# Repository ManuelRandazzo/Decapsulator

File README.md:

# Decapsulator

<p align="center">
  <em>Repo condiviso con il Gruppo 1 ITS 24-26 con programma del macchinario</em>
</p>

---

## Overview
**Decapsulator** è il prototipo di un macchinario nato con lo scopo principale di ridurre rifiuti secchi automatizzando un processo ripetitivo, che tende ad essere evitato e talvolta può diventare pericoloso se non si prestano le dovute attenzioni che è quello di aprire le capsule esauste per poter separare il caffè dall'involucro esterno.

**Sedi**: 
- **IIS Einaudi-Scarpa** : Via Sansovino, 6, 31044 Montebelluna (TV)
- **IPSIA Barsanti-Galilei** : Via Avenale, 6, 31033 Castelfranco Veneto (TV) 

---

## Intended Use 
Prototipo a scopo didattico, non destinato alla vendita o all'uso continuativo. In caso di vendita a scopo commerciale saranno da integrare tutti i dispositivi di sicurezza descritti nelle norme vigenti nella data di revisione e modifica del prototipo successiva a quella descritta dal documento di uso e manutenzione. 

---

## Features
- Automatizzazione della separazione delle capsule dal caffè
- Orientato alla facilità di utilizzo e di manutenzione
- FreeRTOS per avere un controllo real time del processo
- Sicurezza del macchinario
- Prototipo modulabile per diversi tipi di capsule cambiando pochissimi componenti
- Il suo sviluppo ha contribuito in piccola parte al mondo dell'Open Hardware di disegni CAD 3D.
- Design compatto rivolto ad un ambiente domestico

---

## Authors
- ***Manuel Randazzo*** - Firmware Designer, Backend Firmware Developer, Integration Developer, Firmware Tester, Electrical Designer, Electrical tester, Mechanical Designer, Documentation Contributor.
- ***Alessio Pisan*** - Electrical Designer, Electrical Tester, Frontend Firmware Developer, Backend Firmware Developer, Firmware Tester, Documentation Contributor.
- ***Riccardo Pavanetto*** - Mechanical Designer, Mechanical Designer
- ***Federico Dorigo*** - Scrum Master, Procurement Coordinator, Documentation Coordinator, Payroll Administrator
- ***Christian Poletti*** - Documentation Contributor
- ***Arun James Thanamcheril*** - Documentation Contributor

<p align="center">
    <em>Foto del gruppo 1 ITS 24-25 - foto scattata nel 2025.</em>
    <em>Partendo da sinistra : Manuel, Christian, Alessio, Riccardo e Federico</em>
</p>

<p align="center">
    <em>Foto del gruppo 1 ITS 25-26 - foto scattata nel 2026.</em>
    <em>Partendo da sinistra : Federico, Christian, Riccardo, Arun James, Manuel e Alessio</em>
</p>

---

## Dichiarazione Di Conformità CE Del Prototipo
Il presente prototipo è stato progettato seguendo i criteri di sicurezza delle varie direttive:  
- ***Direttiva Macchine 2006/42/CE***: Poiché l'apparecchio presenta organi in movimento, tra cui tamburo rotante, paratia di selezionatura servo-attivata e punzone, i quali comportano rischi meccanici.

- ***Direttiva Bassa Tensione (LVD) 2014/35/UE***: Consultata per la sicurezza dei componenti elettrici e dei circuiti di alimentazione.

- ***Direttiva Compatibilità Elettromagnetica (EMC) 2014/30/UE***: Applicabile per garantire che l’elettronica non interferisca con altre apparecchiature circostanti al macchinario.

- ***Direttiva RoHS 2011/65/UE***: Consultata per garantire l'assenza di sostanze pericolose nei componenti elettronici e nei materiali di apporto. 

Norme armonizzate applicate :
- ***UNI EN ISO 12100:2010***: Sicurezza del macchinario - Principi generali di progettazione - Valutazione e attenuazione del rischio. 

- ***UNI EN ISO 13857:2020***: Distanze di sicurezza per impedire il raggiungimento di zone pericolose con gli arti superiori (utilizzata per dimensionare l'imbocco delle capsule e i carter del tamburo).

- ***UNI EN ISO 14119:2013***: Dispositivi di interblocco associati ai ripari (utilizzata per la scelta e l'installazione del micro-switch di sicurezza sul coperchio).

- ***CEI EN 60204-1***: Sicurezza dell'equipaggiamento elettrico delle macchine (utilizzata per lo schema elettrico e funzionale). 

---

## Disegno Prototipo E Componenti Principali
- ### **Parte Meccanica**

<p align="center">
  <em>Figura 1 — Architettura generale del Decapsulator</em>
</p>
 
**Tabella Componenti :**

| N° |  Descrizione  |
|----|---------------|
| 1  | Profili in alluminio 30x30 cm |
| 2  | Magazzino verticale capsule |
| 3  | Paratia di selezionatura servoattivata del magazzino verticale |
| 4  | Tamburo di posizionamento |
| 5  | Zona di Punzonatura e Raschiatura |
| 6  | Motore passo-passo del Punzone e Raschiatore |
| 7  | Display dell’interfaccia uomo-macchina (HMI) |
| 8  | Scheda elettronica |
| 9  | Griglia di protezione parte elettronica |
| 10 | Ventola di raffreddamento (lato sinistro del macchinario) |

<p align="center">
  <em>Figura 2 — Magazzino Cialde : Serve per stoccare le capsule prima che vengano </em>
</p>

<p align="center">
  <em>Figura 3 — Tamburo : Serve per trasportare la capsula nelle varie fasi di lavorazione (Acquisizione, Punzonatura, Raschiatura, Espulsione)</em>
</p>

- ### **Parte Elettronica**

<p align="center">
  <em>Figura 4 — Scheda di controllo del Decapsulator</em>
</p>

<p align="center">
  <em>Figura 5 — Scheda HMI del Decapsulator</em>
</p>

<p align="center">
  <em>Figura 5 — Scheda HMI del Decapsulator - Vista retro</em>
</p>

<p align="center">
  <em>Figura 6 — Schede del "Magazzino Cialde" del Decapsulator, rappresentano due foto transistor e due LED IR, inoltre su una scheda è presente il connettore 3 poli del servomotore della "Paratia"</em>
</p>

---

## Sequenza Di Funzionamento Automatico Del Decapsulator
Il "Decapsulator" quando viene pilotato in modalità automatica per aprire le capsule di caffè segue questo diagramma :

Il quale temporalmente si traduce in questa sequenza osservando i componenti :

---

## Dati Sui Motori Utilizzati
Le librerie del driver DRV8825 sono state sviluppate interamente da Manuel Randazzo il quale si è preoccupato di studiare e testare l'hardware, consultare la documentazione ufficiale per poter integrare al meglio la libreria che può essere inclusa così :
```C++
#include "DRV8825_Decapsulator.hpp"
```
oppure includendo la libreria del Motion Controller che già utilizza internamente la precedente libreria e che permette una gestione più semplice del Motore :
```C++
#include "MotionControl.hpp"
```

**Flow chart MotionController**

<p align="center">
  <em>Figura 7 — Flow chart MotionController</em>
</p>

**Simulazione Grafico Coppia-Velocità Motori Stepper**

<p align="center">
  <em>Figura 8 — Simulazione curva di coppia dei motori stepper con MATLAB</em>
</p>

---

## Diagnostica E Troubleshooting
Vi è una sezione dedicata per accedere alle impostazioni del manutentore direttamente dall'HMI del macchinario.

Per aiutare il manutentore ad individuare i problemi è possibile ottenere dei privilegi elevati attraverso un login e di conseguenza accedere alla pagina di diagnostica composta dal registro eventi (***Log***) del macchinario e dal movimento manuale (***Jog***) dei motori passo-passo del tamburo rotante e del punzone.

Per maggiori informazioni riguardo a come utilizzare la pagina di manutenzione consultare il manuale di uso e manutenzione alla sezione ***"9.4 Manutenzione tramite pagina di diagnostica sull’interfaccia utente"***.

- Come accedere alla pagina di diagnostica dalla GUI:  

1. Individuare nella pagina principale l’icona dell’ingranaggio indicata in figura

2. Inserire la password unica fornita ai manutentori specializzati

- Come navigare nella pagina di diagnostica dalla GUI, riferimento alla sezione 9.4 del manuale di uso e manutenzione:  

1. Se si vogliono visualizzare i ***LOG*** del macchinario premere il pulsante "Logger" in alto a sinistra della pagina di diagnostica come in figura:

1.1. Una volta selezionato il Logger si vedrà questa pagina da cui si potrà refreshare i logs oppure cancellarli per avere una pagina più pulita con i tasti in figura:

2. Se si vogliono comandare in modalità manuale i motori del macchinario con il ***JOG*** premere il pulsante "Jogger" in alto a destra della pagina di diagnostica come in figura:

2.1. Nota: non sarà possibile aggedere alla pagina "Jogger" se il ciclo automatico è stato avviato e non è stato messo in STOP oppure non è finito e si potrà vedere il seguente messaggio:

2.2. Una volta selezionato il Jogger si vedrà questa pagina da cui si potrà comandare indipendemente i motori e visualizzare gli stati dei sensori di finecorsa:

3. Se si vuole calibrare il display touch premere il pulsante in basso a sinistra della pagina di diagnostica e seguire le istruzioni fornite a display come in figura:

4. Se si vogliono inserire nuove credenziali per il WiFi premere il pulsante in basso a destra della pagina di diagnostica come in figura:

4.1. Una volta selezionata la pagina di configurazione del WiFi verrà visualizzata questa pagina:

<p align="center">
  <em>Nota : il WiFi consente al macchinario di fare l'upload del firmware tramite Over The Air (OTA), di far loggare in MQTT i messaggi del macchinario e soprattutto di sincronizzare il Real Time Clock (RTC) tramite server NTP così da visualizzare l'ora esatta</em>
</p>

---

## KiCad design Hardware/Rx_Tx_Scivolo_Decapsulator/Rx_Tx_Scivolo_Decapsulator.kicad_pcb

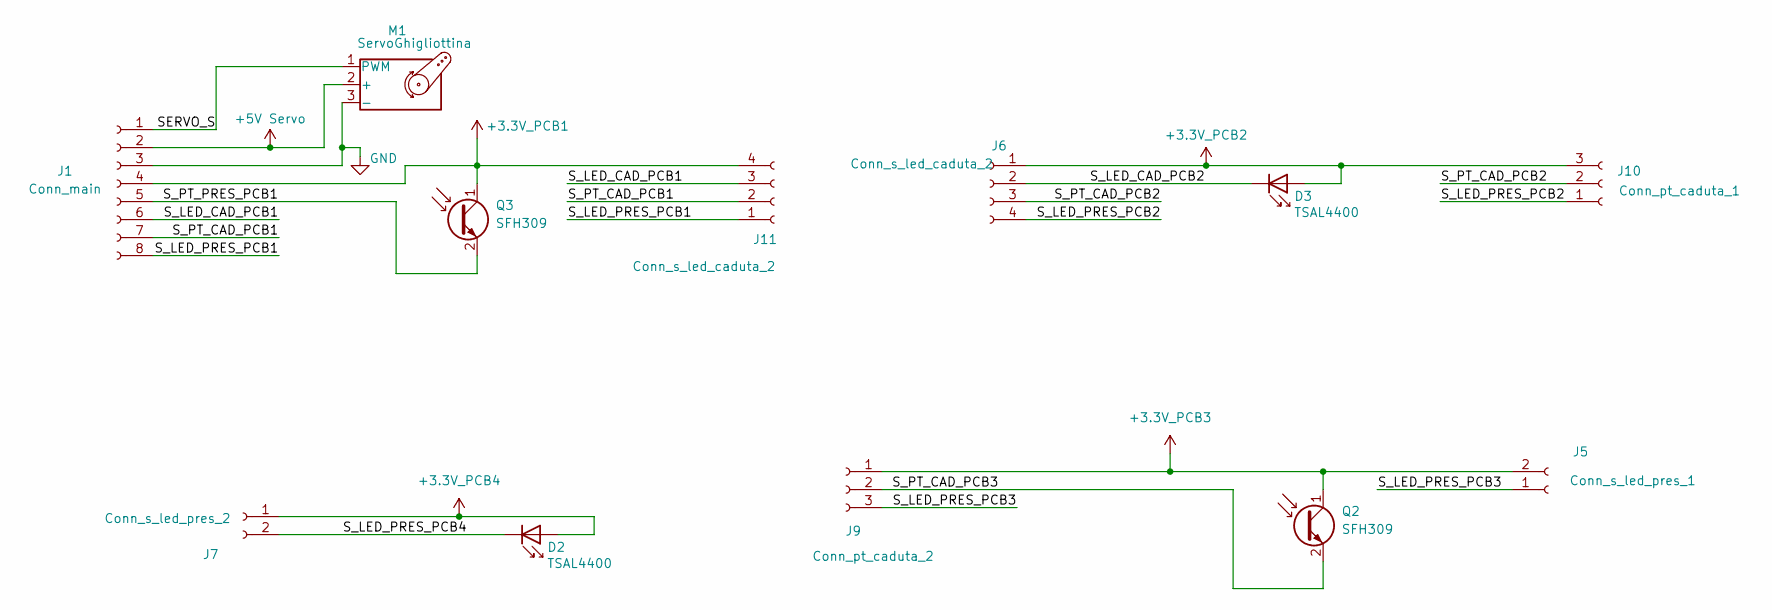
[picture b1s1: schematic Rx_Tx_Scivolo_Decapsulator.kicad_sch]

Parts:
D2, D3: TSAL4400; LED_D3.0mm_Clear
J1: Conn_main; JST_PH_S8B-PH-SM4-TB_1x08-1MP_P2.00mm_Horizontal
J5: Conn_s_led_pres_1; JST_PH_S2B-PH-SM4-TB_1x02-1MP_P2.00mm_Horizontal
J6, J11: Conn_s_led_caduta_2; JST_PH_S4B-PH-SM4-TB_1x04-1MP_P2.00mm_Horizontal
J7: Conn_s_led_pres_2; JST_PH_S2B-PH-SM4-TB_1x02-1MP_P2.00mm_Horizontal
J9: Conn_pt_caduta_2; JST_PH_S3B-PH-SM4-TB_1x03-1MP_P2.00mm_Horizontal
J10: Conn_pt_caduta_1; JST_PH_S3B-PH-SM4-TB_1x03-1MP_P2.00mm_Horizontal
M1: ServoGhigliottina; PinHeader_1x03_P2.54mm_Vertical_SMD_Pin1Right
Q2, Q3: SFH309; LED_D3.0mm_IRBlack

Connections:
+3.3V_PCB1: J1.4, J11.4, Q3.1 (C)
+3.3V_PCB2: D3.2 (A), J6.1, J10.3
+3.3V_PCB3: J5.2, J9.1, Q2.1 (C)
+3.3V_PCB4: D2.2 (A), J7.1
+5V Servo: J1.2, M1.2 (+)
/SERVO_S: J1.1, M1.1 (PWM)
/S_LED_CAD_PCB1: J1.6, J11.3
/S_LED_CAD_PCB2: D3.1 (K), J6.2
/S_LED_PRES_PCB1: J1.8, J11.1
/S_LED_PRES_PCB2: J6.4, J10.1
/S_LED_PRES_PCB3: J5.1, J9.3
/S_LED_PRES_PCB4: D2.1 (K), J7.2
/S_PT_CAD_PCB1: J1.7, J11.2
/S_PT_CAD_PCB2: J6.3, J10.2
/S_PT_CAD_PCB3: J9.2, Q2.2 (E)
/S_PT_PRES_PCB1: J1.5, Q3.2 (E)
GND: J1.3, J1.MP, M1.3 (-)

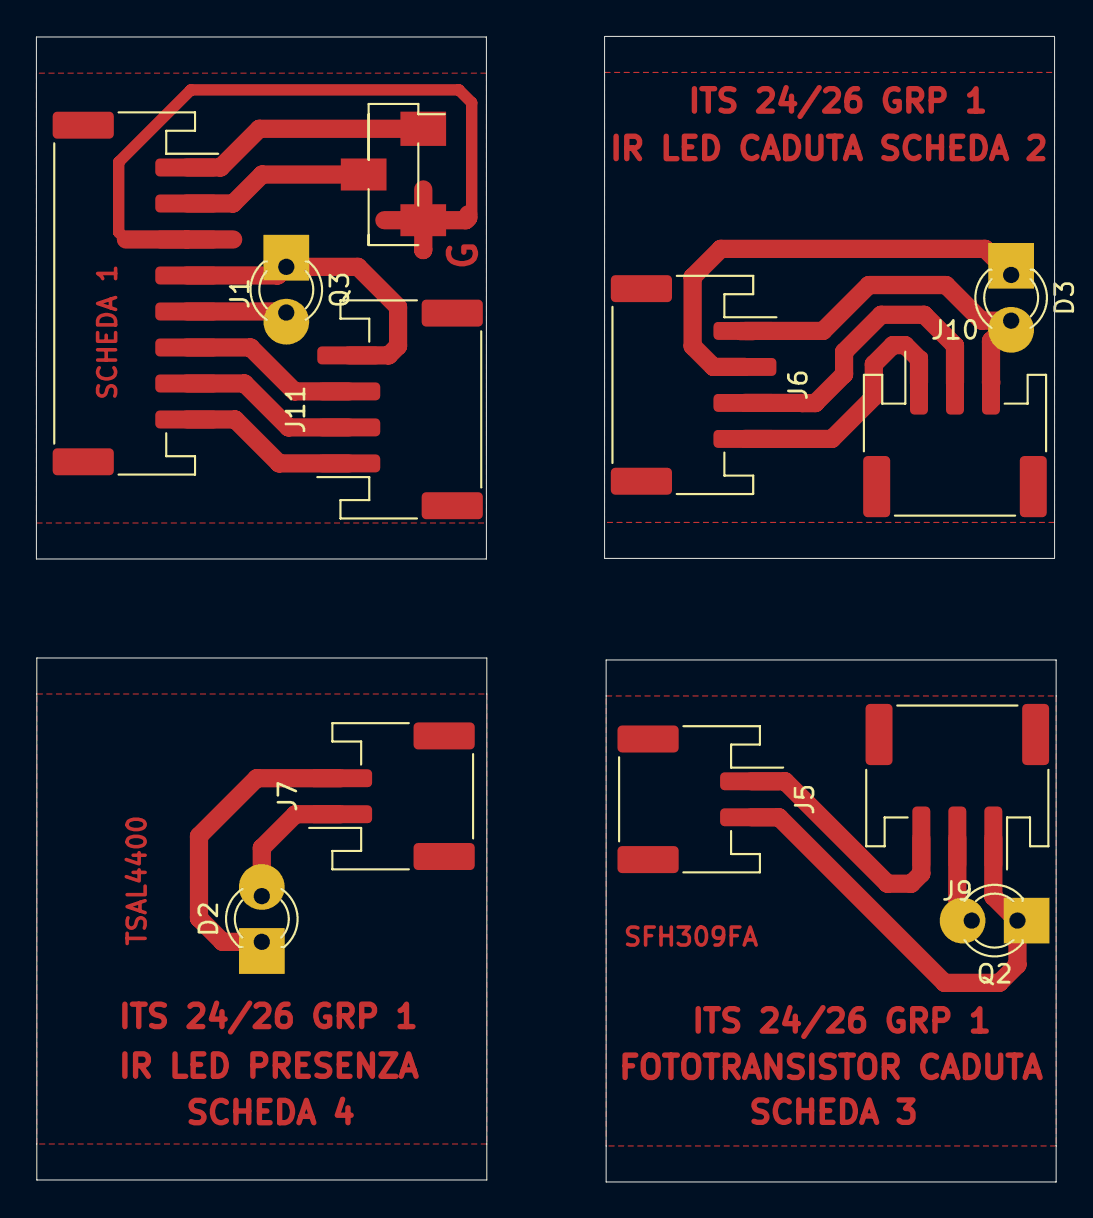
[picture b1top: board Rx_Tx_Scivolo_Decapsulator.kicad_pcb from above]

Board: 2 copper layers, 56.7 x 63.6 mm, 12 parts (0 on the bottom side), 17 nets.

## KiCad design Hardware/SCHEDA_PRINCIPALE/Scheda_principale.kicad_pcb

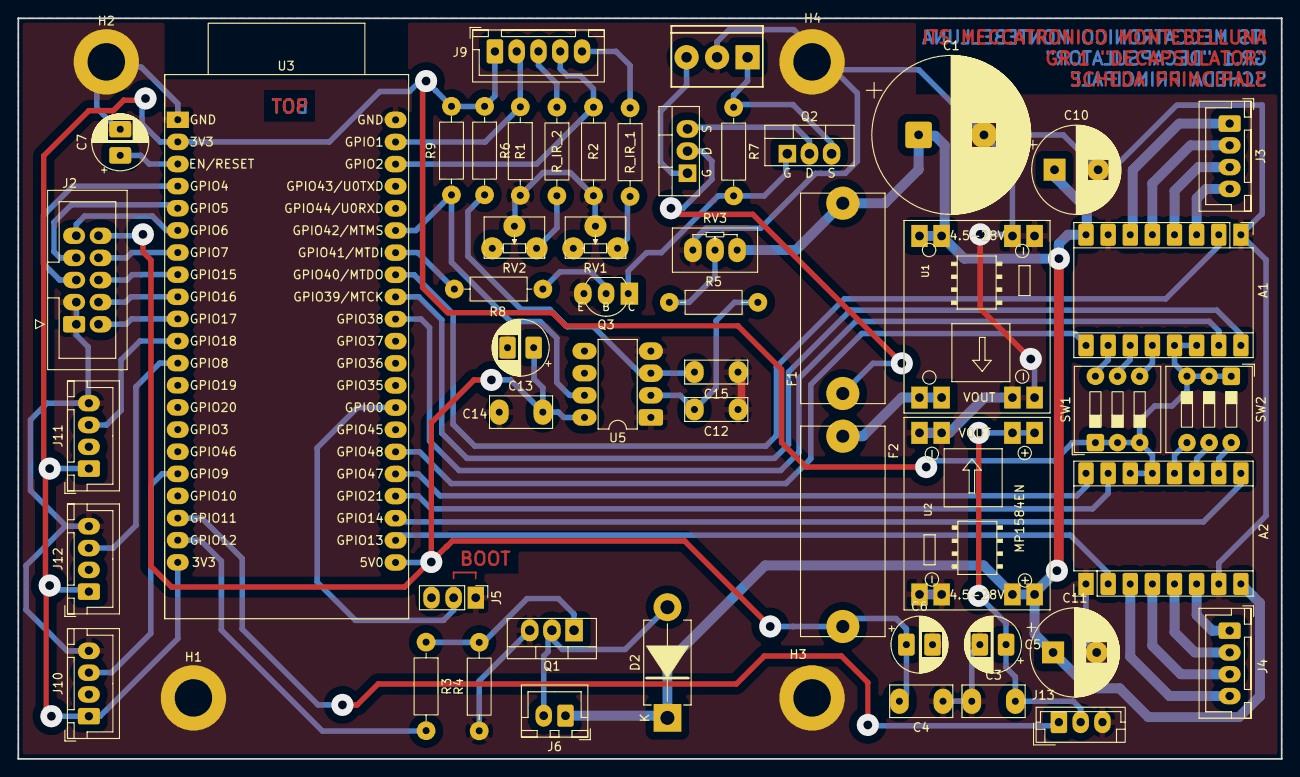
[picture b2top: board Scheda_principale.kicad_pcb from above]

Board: 2 copper layers, 145.0 x 85.0 mm, 56 parts (0 on the bottom side), 61 nets.

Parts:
A1: Driver_motore_ralla; DRV8825
A2: Driver_motore_Punz; DRV8825
C1: 4700uF; CP_Radial_D18.0mm_P7.50mm
C3, C4: 330nF; C_Rect_L7.0mm_W3.5mm_P5.00mm
C5, C6, C13: 47uF; CP_Radial_D6.3mm_P2.50mm
C7: 10uF; CP_Radial_D6.3mm_P2.50mm
C10, C11: 470uF 35V; CP_Radial_D10.0mm_P5.00mm
C12, C15: 22nF; C_Rect_L7.0mm_W2.5mm_P5.00mm
C14: 100nF; C_Rect_L7.0mm_W3.5mm_P5.00mm
D1: SDT10A100CT; TO-220-3_Vertical_GDS
D2: 1N5822; D_DO-201AD_P12.70mm_Horizontal
F1, F2: Fuse; FUSE_4527
H1, H2, H3, H4: MountingHole_Pad; MountingHole_4.3mm_M4_DIN965_Pad
J1: Screw_Terminal_01x03; ScrewTerminal_1x03_P3.5mm_Blue
J2: Conn HMI; IDC-Header_2x05_P2.54mm_Vertical
J3: Conn_Mot_Ralla; JST_XH_B4B-XH-A_1x04_P2.50mm_Vertical
J4: Conn_Mot_Punz; JST_XH_B4B-XH-A_1x04_P2.50mm_Vertical
J5: Conn_BT_MCU; PinHeader_1x03_P2.54mm_Vertical
J6: Conn_Vent1; JST_XH_B2B-XH-A_1x02_P2.50mm_Vertical
J9: Conn_Phototrans; JST_XH_B5B-XH-A_1x05_P2.50mm_Vertical
J10: Conn_hall1; JST_XH_B4B-XH-A_1x04_P2.50mm_Vertical
J11: Conn_hall2; JST_XH_B4B-XH-A_1x04_P2.50mm_Vertical
J12: Conn_hall3; JST_XH_B4B-XH-A_1x04_P2.50mm_Vertical
J13: Conn_Servo; JST_EH_B3B-EH-A_1x03_P2.50mm_Vertical
Q1: IRLZ44N; TO-220-3_Vertical
Q2: IRF9540N; TO-220-3_Vertical_GDS
Q3: BC547B
R1, R2: 47k; R_Axial_DIN0207_L6.3mm_D2.5mm_P10.16mm_Horizontal
R3: 220; R_Axial_DIN0207_L6.3mm_D2.5mm_P10.16mm_Horizontal
R4: 10k; R_Axial_DIN0207_L6.3mm_D2.5mm_P10.16mm_Horizontal
R5, R6: 47K; R_Axial_DIN0207_L6.3mm_D2.5mm_P10.16mm_Horizontal
R7: 15k; R_Axial_DIN0207_L6.3mm_D2.5mm_P10.16mm_Horizontal
R8: 33k; R_Axial_DIN0207_L6.3mm_D2.5mm_P10.16mm_Horizontal
R9: 100k; R_Axial_DIN0207_L6.3mm_D2.5mm_P10.16mm_Horizontal
RV1, RV2: R_Potentiometer; Potentiometer_Bourns_3266W_Vertical
RV3: R_Potentiometer; Potentiometer_Bourns_3296W_Vertical
R_IR_1, R_IR_2: 27R - 1/4W; R_Axial_DIN0207_L6.3mm_D2.5mm_P10.16mm_Horizontal
SW1, SW2: SW_DIP_x03; SW_DIP_SPSTx03_Slide_9.78x9.8mm_W7.62mm_P2.54mm
U1, U2: MP1584
U3: ESP32-S3-DevKitC
U5: LM311; DIP-8_W7.62mm_LongPads

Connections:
+3V3: A1.13 (~RST), A1.14 (~SLP), A2.13 (~RST), A2.14 (~SLP), J9.1, J10.1, J11.1, J12.1, R6.1, R9.2, SW1.1, SW1.2, SW1.3, SW2.1, SW2.2, SW2.3, U3.3V3
+5V: C4.2, C6.1, C13.1, C14.2, F2.2, J2.10, U3.5V, U5.8 (V+)
+5V_SERVO: C3.2, C5.1, J13.2, U2.7 (VOUT1+), U2.8 (VOUT2+)
+9V: D1.3 (A1), Q2.2 (D)
+24V: A1.8 (VMOT), A2.8 (VMOT), C1.1, C10.1, C11.1, D2.1 (K), F1.2, J6.1, RV3.1, U1.3 (VIN1+), U1.4 (VIN2+), U2.3 (VIN1+), U2.4 (VIN2+)
/Project Architecture/Section A - Scheda Principale/Interface A - Interconnects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: J11.3, U3.18 (GPIO18/ADC2_CH7)
/Project Architecture/Section A - Scheda Principale/Interface A - Interconnects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: J12.3, U3.8 (GPIO8/ADC1_CH7)
/Project Architecture/Section A - Scheda Principale/Interface A - Interconnects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: J10.3, U3.9 (GPIO9/ADC1_CH8)
/Project Architecture/Section A - Scheda Principale/Interface A - Interconnects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: J2.2, U3.17 (GPIO17/ADC2_CH6)
/Project Architecture/Section A - Scheda Principale/Interface A - Interconnects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: J2.8, U3.7 (GPIO7/ADC1_CH6)
/Project Architecture/Section A - Scheda Principale/Interface A - Interconnects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: J2.9, U3.6 (GPIO6/ADC1_CH5)
/Project Architecture/Section A - Scheda Principale/Interface A - Interconnects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: J2.6, U3.15 (GPIO15/ADC2_CH4/32K_P)
/Project Architecture/Section A - Scheda Principale/Interface A - Interconnects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: J2.4, U3.16 (GPIO16/ADC2_CH5/32K_N)
/Project Architecture/Section A - Scheda Principale/Interface A - Interconnects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: J2.7, U3.5 (GPIO5/ADC1_CH4)
/Project Architecture/Section A - Scheda Principale/Interface A - Interconnects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: J2.5, U3.4 (GPIO4/ADC1_CH3)
/Project Architecture/Section A - Scheda Principale/Interface A - Interconnects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: A2.4 (A1), J4.3
/Project Architecture/Section A - Scheda Principale/Interface A - Interconnects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: A2.3 (A2), J4.4
/Project Architecture/Section A - Scheda Principale/Interface A - Interconnects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: A2.5 (B1), J4.2
/Project Architecture/Section A - Scheda Principale/Interface A - Interconnects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: A2.6 (B2), J4.1
/Project Architecture/Section A - Scheda Principale/Interface A - Interconnects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: J13.1, U3.11 (GPIO11/ADC2_CH0)
/Project Architecture/Section A - Scheda Principale/Interface A - Interconnects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: A1.4 (A1), J3.3
/Project Architecture/Section A - Scheda Principale/Interface A - Interconnects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: A1.3 (A2), J3.4
/Project Architecture/Section A - Scheda Principale/Interface A - Interconnects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: A1.5 (B1), J3.2
/Project Architecture/Section A - Scheda Principale/Interface A - Interconnects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: A1.6 (B2), J3.1
/Project Architecture/Section A - Scheda Principale/Interface A - Interconnects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: J9.3, R_IR_2.1
/Project Architecture/Section A - Scheda Principale/Interface A - Interconnects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: J9.5, R_IR_1.1
/Project Architecture/Section A - Scheda Principale/Interface A - Interconnects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: J9.4, R2.1, U3.2 (GPIO2/ADC1_CH1)
/Project Architecture/Section A - Scheda Principale/Interface A - Interconnects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: J9.2, R1.1, U3.1 (GPIO1/ADC1_CH0)
/Project Architecture/Section A - Scheda Principale/MCU/AK_DO: R9.1, U3.42 (GPIO42/MTMS), U5.7
/Project Architecture/Section A - Scheda Principale/MCU/AK_INT: R8.2, U3.41 (GPIO41/MTDI)
/Project Architecture/Section A - Scheda Principale/MCU/BOOT_MCU: J5.2, U3.0 (GPIO0)
/Project Architecture/Section A - Scheda Principale/MCU/CONTR_VENT: R3.2, U3.12 (GPIO12/ADC2_CH1)
/Project Architecture/Section A - Scheda Principale/MCU/PUNZ_DIRECTION_DRV: A2.16 (DIR), U3.47 (GPIO47)
/Project Architecture/Section A - Scheda Principale/MCU/PUNZ_ENABLE_DRV: A2.9 (~EN), U3.14 (GPIO14/ADC2_CH3)
/Project Architecture/Section A - Scheda Principale/MCU/PUNZ_FAULT: A2.2 (~FLT), U3.13 (GPIO13/ADC2_CH2)
/Project Architecture/Section A - Scheda Principale/MCU/PUNZ_STEP_DRV: A2.15 (STEP), U3.21 (GPIO21)
/Project Architecture/Section A - Scheda Principale/MCU/RALLA_DIRECTION_DRV: A1.16 (DIR), U3.39 (GPIO39/MTCK)
/Project Architecture/Section A - Scheda Principale/MCU/RALLA_ENABLE_DRV: A1.9 (~EN), U3.48 (GPIO48)
/Project Architecture/Section A - Scheda Principale/MCU/RALLA_FAULT: A1.2 (~FLT), U3.40 (GPIO40/MTDO)
/Project Architecture/Section A - Scheda Principale/MCU/RALLA_STEP_DRV: A1.15 (STEP), U3.38 (GPIO38)
/Project Architecture/Section A - Scheda Principale/Misc - Autokill/VBAT: J1.1, Q2.3 (S), R7.1
GND: A1.1 (GND), A1.7 (GND), A2.1 (GND), A2.7 (GND), C1.2, C3.1, C4.1, C5.2, C6.2, C7.2, C10.2, C11.2, C12.1, C13.2, C14.1, C15.1, H1.1, H2.1, H3.1, H4.1, J1.2, J2.1, J2.3, J5.1, J10.4, J11.4, J12.4, J13.3, Q1.3 (S), Q3.3 (E), R1.2, R2.2, R4.1, RV1.2, RV2.2, RV3.3, U1.1 (VIN1-), U1.2 (VIN2-), U1.5 (VOUT1-), U1.6 (VOUT2-), U2.1 (VIN1-), U2.2 (VIN2-), U2.5 (VOUT1-), U2.6 (VOUT2-), U3.G (GND), U5.1 (GND), U5.4 (V-)
unnamed: A1.10 (M0), SW1.6
unnamed: A1.11 (M1), SW1.5
unnamed: A1.12 (M2), SW1.4
unnamed: A2.10 (M0), SW2.6
unnamed: A2.11 (M1), SW2.5
unnamed: A2.12 (M2), SW2.4
unnamed: D1.1 (A2), J1.3
unnamed: D1.2 (K), F1.1
unnamed: D2.2 (A), J6.2, Q1.2 (D)
unnamed: Q1.1 (G), R3.1, R4.2
unnamed: Q2.1 (G), Q3.1 (C), R7.2
unnamed: Q3.2 (B), R8.1
unnamed: R5.1, RV3.2
unnamed: RV1.3, R_IR_1.2
unnamed: RV2.3, R_IR_2.2
unnamed: F2.1, U1.7 (VOUT1+), U1.8 (VOUT2+)
unnamed: C7.1, U3.RST (CHIP_PU)
unnamed: C12.2, R5.2, U5.2 (+)
unnamed: C15.2, R6.2, U5.3 (-)

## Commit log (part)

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2025-12-05 Primo caricamento del programma del Decapsulator sul repo dedicato in GitHub
2025-12-07 UPDATE: WiFi_secrets now called WiFi_Config
2025-12-21 refactor(Motion Controller): aggiornata la gestione dovuto alla modifica della libreria del DRV8825
2025-12-25 refactor(stepper driver): migliorata la gestione del DRV8825 per girare in una task già esistente
2026-01-03 refactor(MotionControl): Portata ad un livello stabile la gestione del motion in quanto ora è capace di far effetivamente girare il motore :)
2026-01-03 fixed(Debug handle): Ora in caso si tolga il logger MQTT non vi saranno errori di compilazione dovuti all'ommisione del controllo della funzione 'DebugOverrideVar'
2026-01-04 Revert "fixed(Debug handle): Ora in caso si tolga il logger MQTT non vi saranno errori di compilazione dovuti all'ommisione del controllo della funzione 'DebugOverrideVar'"
    This reverts commit 9834df87bfcddb4dfee4a810bb896123dcf9482b.
2026-01-04 test(tamburo): il programma del tamburo è ancora in fase di test
2026-01-29 add(helper debounce): aggiunto un helper per la gestione dei pin input interrupt e polling con debounce
2026-03-01 Trying to Fix(WiFi.h not found):provo a fare un push per vedere se builda
2026-03-14 refactor(debounce pin handler): rivisitata a debuggata e testate la gestione sia del polling che dell'interrupt per i pin di input
2026-03-18 refactor(platformio.ini) : aggiunta l'estensione per la PSRAM
2026-03-19 fixed(Debounce Pin) : fixato tutti i return che non cedevano il semaforo con xSemaphoreGive
2026-04-08 add(remove hardLimits): aggiunta la funzione removeHardLimits e migliorata la gestione degli hard limits durante l'homing
2026-04-08 add(timeout): aggiunto timeout di setup delle task che fa riavviare l'ESP32 se superato
2026-04-08 add(useless datas): rimossi alcuni dati che possono essere facilmente ricreai in automatico dall'ambiente stesso
2026-04-15 refactor(WiFi Start Option): resa disponibilità di non far inizializzare il WiFi, esce un warning all'upload (voluto da me) che dice che non sarà possibile usare il logger e caricare lo sketch da rem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
2026-04-16 changed(WiFi timeout): aumentato il timeout di inizializzazione del WiFi da 4000ms a 5000ms
2026-04-17 add(timeout rmt transmission): aggiunto un timeout di trasmissione dell'rmt di 10ms al posto di un wait infinito
2026-04-17 add(HMI task config): aggiunte le variabili per la task HMI e cambiata la quantità di memoria allocata, la priorità e il delay delle altre task (OTA e MainPrg)
2026-04-28 stable(programma principale): reso stabile e funzionante il programma del Decapsulator, da ora in poi bisogna stare attenti a non rompere il funzionamento
2026-04-28 refactor(DRV8825): rivisitato e migliorato tutto il funzionamento del driver degli stepper DRV8825, ora viene sfruttato molto meglio l'hardware e vengono impiegate meno risorse e si ha sempre un movi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
2026-04-28 delete(contenitori del caffè e delle capsule): non ci sono più i contenitori
2026-05-08 add(FanCtrl) : aggiunta una classe per controllare una ventola tramite l'hardware LEDC (LED Control)
2026-05-10 delete(3D_SchedHMI_Logo.png) : cambiato il nome del file e richiede commit
2026-05-10 add(Jog params) : aggiunti i parametri per la task di JOG
2026-05-11 add(Meccanica)
2026-05-11 cleanup(old repo)
2026-05-12 fix(LISTA TOTALE)
2026-05-12 add(config HMI)
2026-05-13 add(esempio funzioni d'evento) : aggiunto un esempio di come vengono scritte le funzioni degli eventi
2026-05-16 add(HMI generated file) : aggiunti i file generati da squareline nella directory lib/HMI/src al posto di averli nella directory squareline
2026-05-16 add(ui_Object) : aggiunto il file che ha lo scopo di dichiarare dei #define degli oggetti della UI così da poter facilmente usarli nei programmi di jog e principale senza stare troppo attenti su come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
2026-05-16 rename(FotoGruppo1 primo anno)
2026-05-22 add(configurazione tasks) : aggiunti due file separati per avere gli Handlers e le configurazioni delle tasks in un unico file. Tolte dal file "Tasks.hpp"
2026-05-22 add(inizializzazioni IOs e queues HMI) : aggiunta l'inizializzazione degli IOs e le creazioni delle Queues di trasmissione UI e Backend direttamente nella creazione delle task perchè è meglio se iniz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
2026-05-23 refactor(HMI heap) : alzata la memoria dedicata per la task HMI
2026-05-24 fix(TFT Config) : aggiunto il pin SD, invertiti il MISO e il MOSI per un errore sulla scheda principale, rimosse tante righe inutili come dimensioni display e directory "lib/*", rimosse tutte le buil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
2026-05-25 test(ui backend) : test della comunicazione Frontend - Backend
2026-05-25 add(extern della state machine sequenza) : ora anche i programmi esterni possono modificare la state machine per determinare dove si trova il programma principale
2026-05-28 update(lvgl library) : passati dalla lvgl 9.3.0 alla 9.5.0 per adattarsi al passagio da SquareLine Studio a EEZ Studio per lo sviluppo della UI
2026-06-03 remove(semaphore) : rimosso il semaforo poichè inutile
2026-06-03 migrate(User Interface Generated Program) : migrazione dal software "SquareLine Studio" a "EEZ Studio" dovuto a limitazioni del primo e miglioramenti di gestione dell'interfaccia Backend <--> Frontend
2026-06-03 add(SD_Card Init & init AK_OUT) : viene inizializzata anche la SD_Card, è la prima inizializzazione che viene fatta perchè è necessaria per il Logger (se LOG_COPY_TO_SD nel file Debug.hpp è definito)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
2026-06-04 fix(begin fan pin) : risolto il problema per il quale la ventola non veniva inizializzata. Il motivo era che veniva passato fan_pin e non pin alla funzione pinMode nel begin.
2026-06-05 add(External SPI) : aggiunta la possibilità di passare un'istanza SPI (per esempio quella del display) nell'inizializzazione della SD. fix(template methods) : spostati i metodi dal .cpp al .hpp. fix(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
2026-06-06 add(SPI_SD_FREQUENCY) : aggiunto il define per la frequenza dell'SPI per la SD
2026-06-06 add(LV_FONT_MONTSERRAT_xx) : aggiunti i fon usati in eez flow per la UI
    remove(lv_conf_decapsulator_template) : era insensato avere un file template, aveva senso solo quando lv_conf.h stava direttamente con la libreria lvgl
2026-06-09 remove(bypass schermata avvio) : rimosso il bypass scena iniziale di avvio macchina
2026-06-11 add(MAX_COFFEE_CONTAINER) : così da avvisare l'utente che deve svuotare il contenitore del caffè
2026-06-11 add(xTaskDelayUntil) : aggiunto il delay configurato nel file tasks_cfg.hpp (Logger_delay)
2026-06-12 fix(begin()) : risolto un problema legato all'assegnazione del flag "changeOccurred" e del level che sovrascriveva il valore reale portando ad errori
    add(MUTEX_TICKS) : aggiunta la possibilità di far aspettare qualche millisecondo per prendere il semaforo, per ora definito a 100ms massimo
    fix(comments) : aggiustati dei commenti nella definizione della classe e portato tutte le variabili da private a protected
2026-06-13 add(Jog Punzone & Jog Tamburo Queues) : aggiunte le code per sapere se viene fatto jog+ o jog- sia per punzone che per tamburo.
2026-06-15 remove(ui_and_backend_cfg) : rimosso il file della configurazioni delle code di trasmissione tra UI<->Backend perchè con EEZ Studio è diventato superfluo
2026-06-15 exp fix WiFi
2026-06-15 refactor(Jogger) : integrata la comunicazione HMI - Jogger funzionante
2026-06-15 pls exp fiz WiFi 4
2026-06-15 WIP rafactor(WiFi page native vars)
2026-06-17 add dashboard
2026-06-17 add(Time & Date) : aggiunta la visualizzazione della data e dell'ora nella UI. L'RTC viene sincronizzato con il server NTP "pool.ntp.org" ogni 30 minuti per evitare drift accumolati e non dover avere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
2026-06-17 remove(last enables) : eliminate le variabili che memorizzavano l'ultimo stato dell'enable dei motori stepper.
    chore(gradi_per_click and speed_motore) : inizializzati i gradi per click a 360° e le velocità dei motori a 90°/s.
    changed(sensors reading) : ora tutti i sensori HALL vengono letti direttamente dal pin senza il bisogno di leggere lo stato dal puntatore all'istanza dei sensori del MotionController.
    add(Motor Moving LEDs) : aggiunto il cambiamento di stato dei LED che segnalano il movimento dei motori.
    remove(logs) : rimossi i log dopo i test effettuati.
    add(homing abort) : aggiunta la possibilità di abortire l'homing.
    remove(old commented logic) : rimossa tutta la vecchia l
2026-06-18 WIP -> add(second time puncher) : aggiunta una fase in cui il punzone torna giù per poter raschiare meglio la capsula.
2026-06-18 add(SD_LOG_ACTIVE) : ora è possibile disattivare e riattivare facilmente i log della SD in Seriale (non passano nel logger).
    upgrade(file.read()) : ora viene passato un buffer al posto di dover aggiungere carattere per carattere del file.
2026-06-18 remove(duplicated psram-cache-issue)
2026-06-18 upgrade(lvgl config) : ora la configurazione della libreria lvgl costa meno in termini di risorse al sistema. In più è stata aumentata la frequenza di aggiornamento del display.
    fix(out of memory issue WiFi Config) : risolto il problema che la UI andava out of memory quando si entrava nelle configurazioni del WiFi
2026-06-20 add(second draw buffer) : aggiunto un secondo draw buffer di disegno.
    moved(buffers from DRAM to PSRAM) : ora i buffer di disegno vengono allocati in PSRAM quindi sono anche più grandi.
    add(MALLOC_CAP_DMA for draw buffers) : aggiunta la possibilità di permettere al DMA di accedere ai draw buffers quando questi si trovano in PSRAM.
2026-06-20 add(salvataggio in microSD WiFi credentials).
2026-06-21 WIP -> refactor(DRV8825) : prima di togliere le accelerazioni
2026-06-21 chore(MainPrg_delay & JogMotori_delay) : aumentato il delay per non fare bottleneck sulla CPU.
2026-06-21 fix qr when error
2026-06-23 fix fine
2026-06-24 add(force clock to sync) : aggiunta una notifica che forza l'RTC di sistema a sincronizzarsi con un server NTP anche se il normale tempo di sync non è stato raggiunto.
2026-06-24 add(clangd for c/c++ compilation)
2026-06-24 add(auto sync at WiFi connection) : forza un'auto sincronizzazione col server NTP quando si è appena connesso al WiFi.
2026-06-24 chore(presenzaCapsule INTR->POLL) : cambiato il metodo di lettura di presenzaCapsule da INTERRUPT a POLLING.
2026-06-24 chore(incremented global task priorities) : aumentate tutte le priorità delle task per essere più varie e soprattutto più distribuite.
2026-06-24 add(touch calibration text string) : aggiunta la stringa delle istruzioni per la calibrazione del touch.
2026-06-24 refactor(homing) : messo l'homing corretto (non testato) del decapsulator.
    remove(legacy accelerations): rimosse completamente le accelerazioni.
    add(xQueue resets) : le queues dei Jog- e Jog+ vengono resettate quando si disabilita il motore per evitare avviamenti accidentali.
2026-06-25 replace(nCicliRimanenti): sostituita nCicliRimanenti con shiftRegisterCapsuleCaricate
2026-06-26 fix(contatori capsule) : aggiunto uno shift register per contare le capsule e sapere esattamente dove sono nel tamburo.
    add(gestione fault motori) : ora i motori fanno aspettare l'utente un po' fino a quando i driver dei motori non si sono raffreddati.
    fix(post Homing position Ralla) : impostato correttamente la posizione post Homing della ralla.
    add(motors attach only when needed) : ora i motori vengoni messi in coppia (abilitati) solo quando serve utilizzarli, il tamburo in realtà rimane sempre in coppia per poter garantire la posizione, se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
2026-06-26 chore(defined decapsulator configurations).
2026-06-28 adjust(RALLA_POST_HOME_POS_CONT & RALLA_POST_HOME_POS) : aggiustati i parametri di Homing del tamburo (ralla).
